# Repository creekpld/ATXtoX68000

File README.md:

# This is not the Repo you are looking for! :alien:

New development is taking place in [gitlab.com/pdylong/ATXtoX68000](https://gitlab.com/pdylong/ATXtoX68000) :ok_hand:.

# ATXtoX68000

An ATX to X68000 Power Supply Adapter

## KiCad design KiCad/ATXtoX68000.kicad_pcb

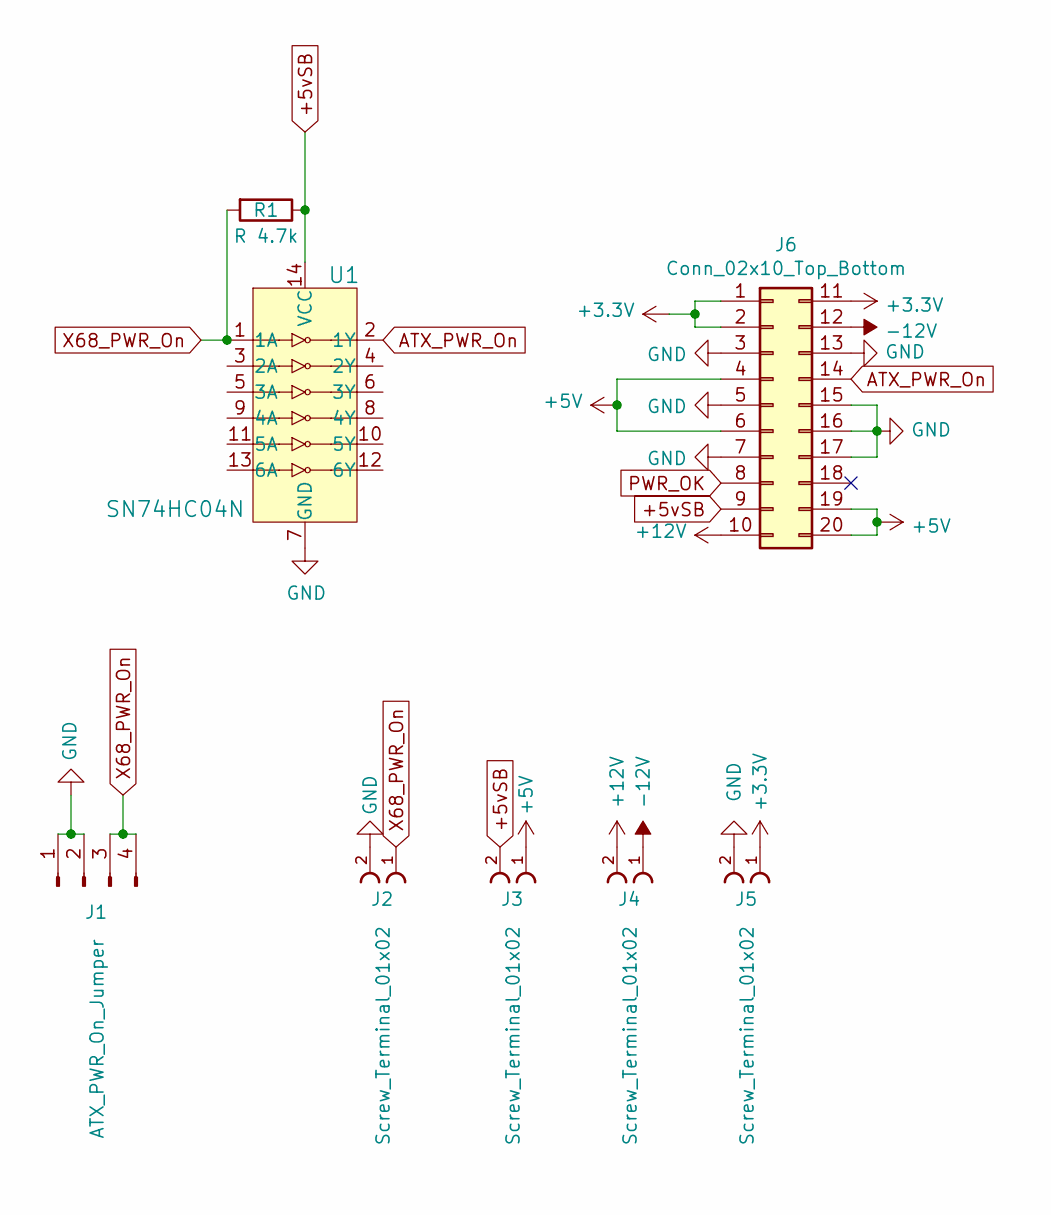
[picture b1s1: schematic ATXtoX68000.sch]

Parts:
J1: ATX_PWR_On_Jumper; PinHeader_1x04_P2.54mm_Vertical
J2: Screw_Terminal_01x02; 691137710002; Digi-Key_PN 732-10955-ND
J3, J4, J5: Screw_Terminal_01x02; 691137710002
J6: Conn_02x10_Top_Bottom; Molex_Mini-Fit_Jr_5566-20A_2x10_P4.20mm_Vertical
R1: R 4.7k; R_Axial_DIN0204_L3.6mm_D1.6mm_P7.62mm_Horizontal
U1: SN74HC04N; DIP-14_W3mm; MPN SN74HC04N; Digi-Key_PN 296-1566-5-ND

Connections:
+3V3: J5.1, J6.1, J6.2, J6.11
+5V: J3.1, J6.4, J6.6, J6.19, J6.20
+5vSB: J3.2, J6.9, R1.1, U1.14 (VCC); also elsewhere on the board
+12V: J4.2, J6.10
-12V: J4.1, J6.12
ATX_PWR_On: J6.14, U1.2 (1Y); also elsewhere on the board
GND: J1.1, J1.2, J2.2, J5.2, J6.3, J6.5, J6.7, J6.13, J6.15, J6.16, J6.17, U1.7 (GND); also elsewhere on the board
PWR_OK: J6.8
X68_PWR_On: J1.3, J1.4, J2.1, R1.2, U1.1 (1A); also elsewhere on the board

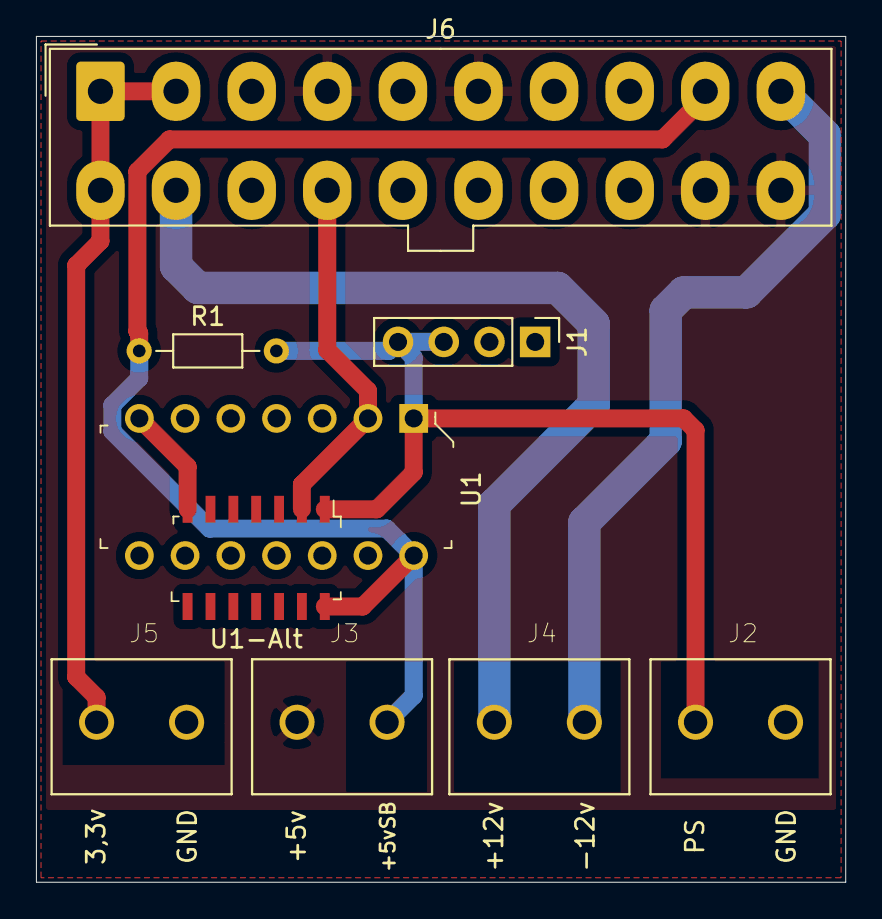
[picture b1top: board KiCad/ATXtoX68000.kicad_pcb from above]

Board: 2 copper layers, 45.0 x 47.0 mm, 9 parts (0 on the bottom side), 8 nets.

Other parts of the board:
U1-Alt: SOIC-14_W3.9mm

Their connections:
+5vSB: U1-Alt.14; also elsewhere on the board
ATX_PWR_On: U1-Alt.2; also elsewhere on the board
GND: U1-Alt.7; also elsewhere on the board
X68_PWR_On: U1-Alt.1; also elsewhere on the board

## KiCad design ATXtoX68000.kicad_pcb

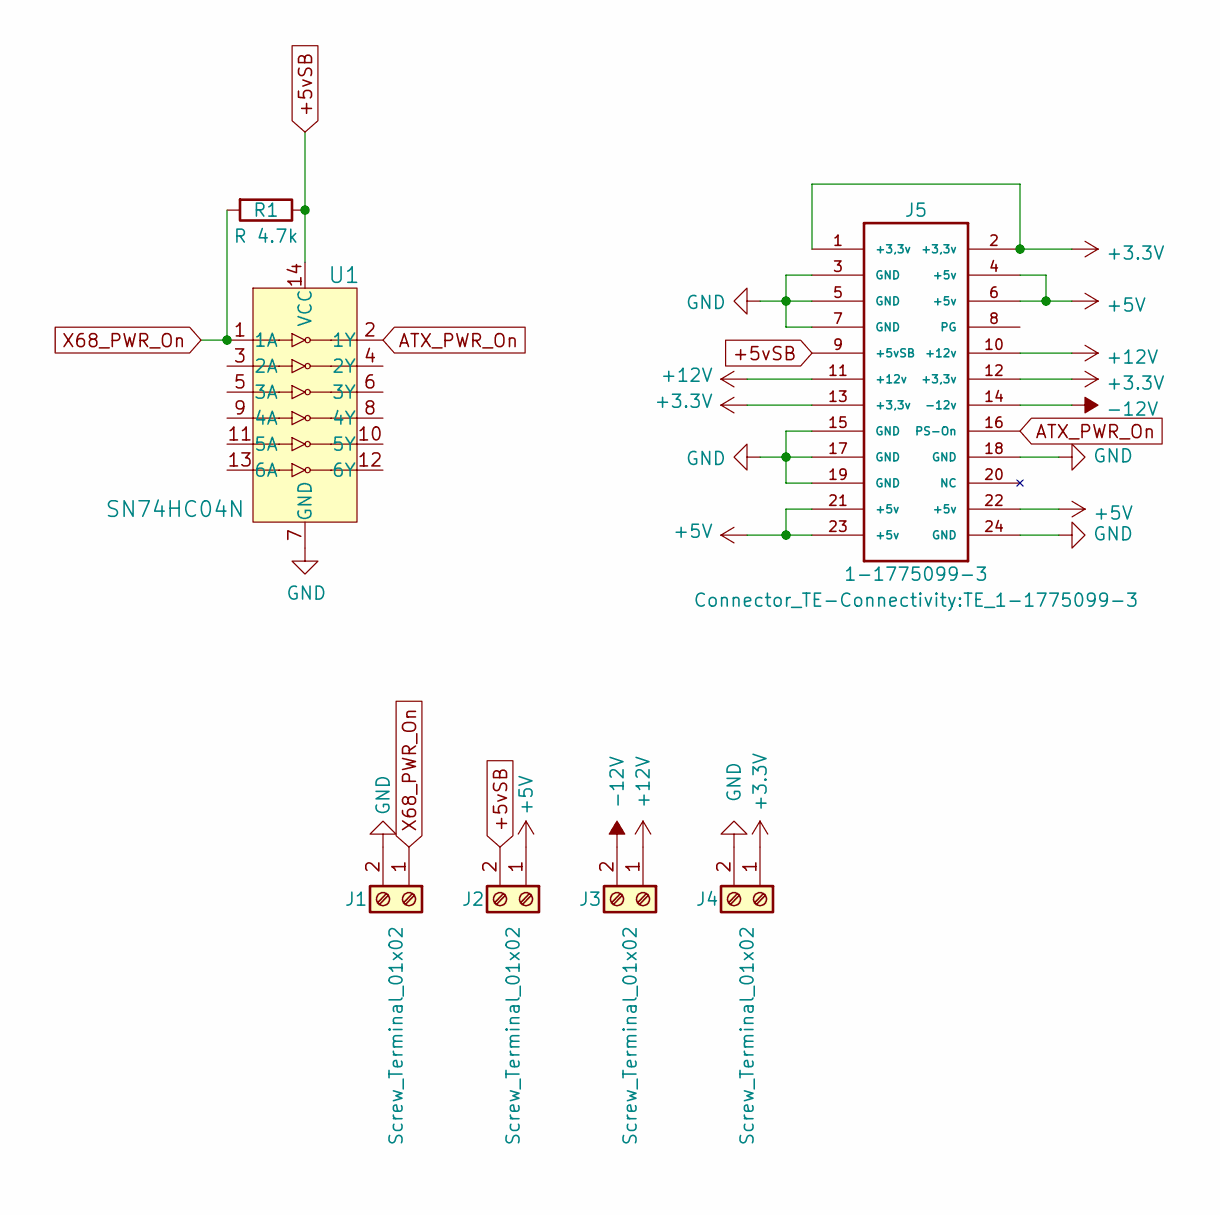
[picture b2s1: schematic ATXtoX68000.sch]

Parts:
J1, J2, J3, J4: Screw_Terminal_01x02; TerminalBlock_Altech_AK300-2_P5.00mm
J5: 1-1775099-3; TE_1-1775099-3
R1: R 4.7k; R_Axial_DIN0204_L3.6mm_D1.6mm_P7.62mm_Horizontal
U1: SN74HC04N; DIP-14_W3mm; MPN SN74HC04N; Digi-Key_PN 296-1566-5-ND

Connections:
+3V3: J4.1, J5.1 (+3,3v), J5.2 (+3,3v), J5.12 (+3,3v), J5.13 (+3,3v)
+5V: J2.1, J5.4 (+5v), J5.6 (+5v), J5.21 (+5v), J5.22 (+5v), J5.23 (+5v)
+5vSB: J2.2, J5.9 (+5vSB), R1.1, U1.14 (VCC)
+12V: J3.1, J5.10 (+12v), J5.11 (+12v)
-12V: J3.2, J5.14 (-12v)
ATX_PWR_On: J5.16 (PS-On), U1.2 (1Y)
GND: J1.2, J4.2, J5.3 (GND), J5.5 (GND), J5.7 (GND), J5.15 (GND), J5.17 (GND), J5.18 (GND), J5.19 (GND), J5.24 (GND), U1.7 (GND)
X68_PWR_On: J1.1, R1.2, U1.1 (1A)

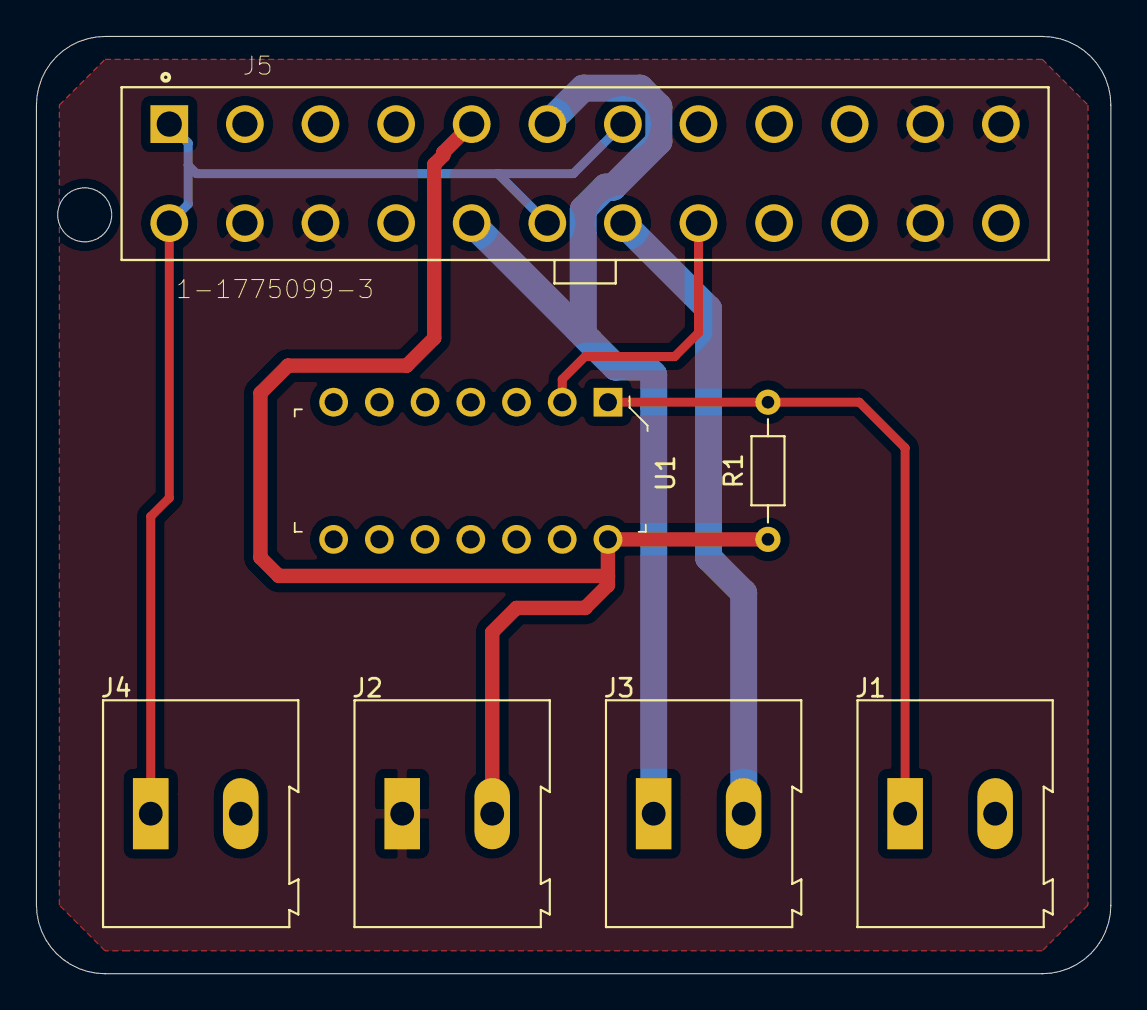
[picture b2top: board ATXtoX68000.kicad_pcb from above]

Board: 2 copper layers, 59.7 x 52.1 mm, 7 parts (0 on the bottom side), 8 nets.

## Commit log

2019-05-24 added .gitignore
2019-05-24 initial stuff commit
2019-05-27 :construction: Work in progress
2020-06-13 :memo: Writing docs.
2020-07-21 Update README.md
    moving out
